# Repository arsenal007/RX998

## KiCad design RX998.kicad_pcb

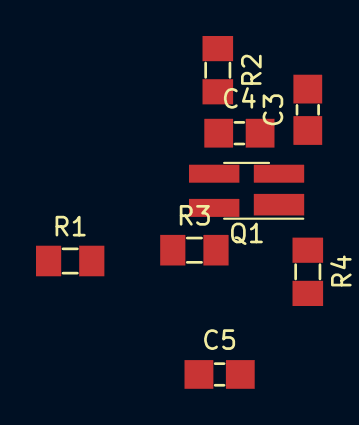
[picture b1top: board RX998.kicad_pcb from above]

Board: 2 copper layers, 8 parts (0 on the bottom side), 6 nets, no tracks yet.

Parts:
C3: 10nF; C_1206_0603
C4, C5: 100nF; C_1206_0603
Q1: BF998; SOT-143_Handsoldering
R1: 100; R_1206_0603
R2: 10k; R_1206_0603
R3: 300; R_1206_0603
R4: 220; R_1206_0603

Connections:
GND: C4.2, C5.2, R4.2
unnamed: R1.2, R2.1
unnamed: C3.1, Q1.2
unnamed: C4.1, Q1.3, R2.2
unnamed: C5.1, Q1.1, R3.2, R4.1
unnamed: Q1.4, R3.1

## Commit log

2019-03-30 first commit, only schematics
